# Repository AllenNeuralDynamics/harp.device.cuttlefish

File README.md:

An 8-channel TTL input-or-output device with programmable square wave output

## Features
* 8x TTL input or output, configurable.
* Direct PC control of IO Pins:
  * set pins configured as output to either HIGH (5V) or LOW (0V)
  * read the state of pins configured as inputs as either HIGH (~5V) or LOW (~0V) at TTL logic levels.
* Programmable square wave generation with many configurable settings:
  * PWM Frequency range: from 0.01Hz to 2KHz
  * Duty Cycle
  * Offset
  * number of pulses (or infinite)
* Input Capture. Configure pins as inputs to detect
  * rising edges (up to 500Hz)
  * falling edges (up to 500Hz)
  * both! (up to 500hz)
* Harp-protocol compliant (serial num: 0x057B).
* Bonus: "passthrough buffer mode." External 3.3V and 5V CMOS devices can use this device as an octal buffer with external pins.

> [!NOTE]
> This board produces digital outputs and measures digital inputs only! For producing high fidelity _analog_ outputs, refer to the [harp.device.quac](https://github.com/AllenNeuralDynamics/harp.device.quad-dac) device.

## Extra Features
* 6-24VDC input (2.1 x 5.5mm barrel jack, positive center)
* reverse polarity protection
* soft start
* isolated USB to avoid forming ground loops with the PC.

## PWM Waveform Setup
Each IO pin is capable of producing a PWM output. Here are the settings available:
* _offset_us_: how long (in microseconds) the output should remain LOW before switching the output HIGH in one period.
* _on_duration_us_: how long (in microseconds) the output should remain HIGH in one period.
* _off_duration_us_: how long (in microseconds) the output should remain LOW in one period.
* _cycles_: how many pulses to produce or zero for infinite pulses until disabled.
* _invert_: whether the output should be inverted (on-time refers to the output being LOW instead).

> [!NOTE]
> Although multiple PWM channels can be set to different settings and produce outputs concurrently, all PWM outputs must be started at the same time.

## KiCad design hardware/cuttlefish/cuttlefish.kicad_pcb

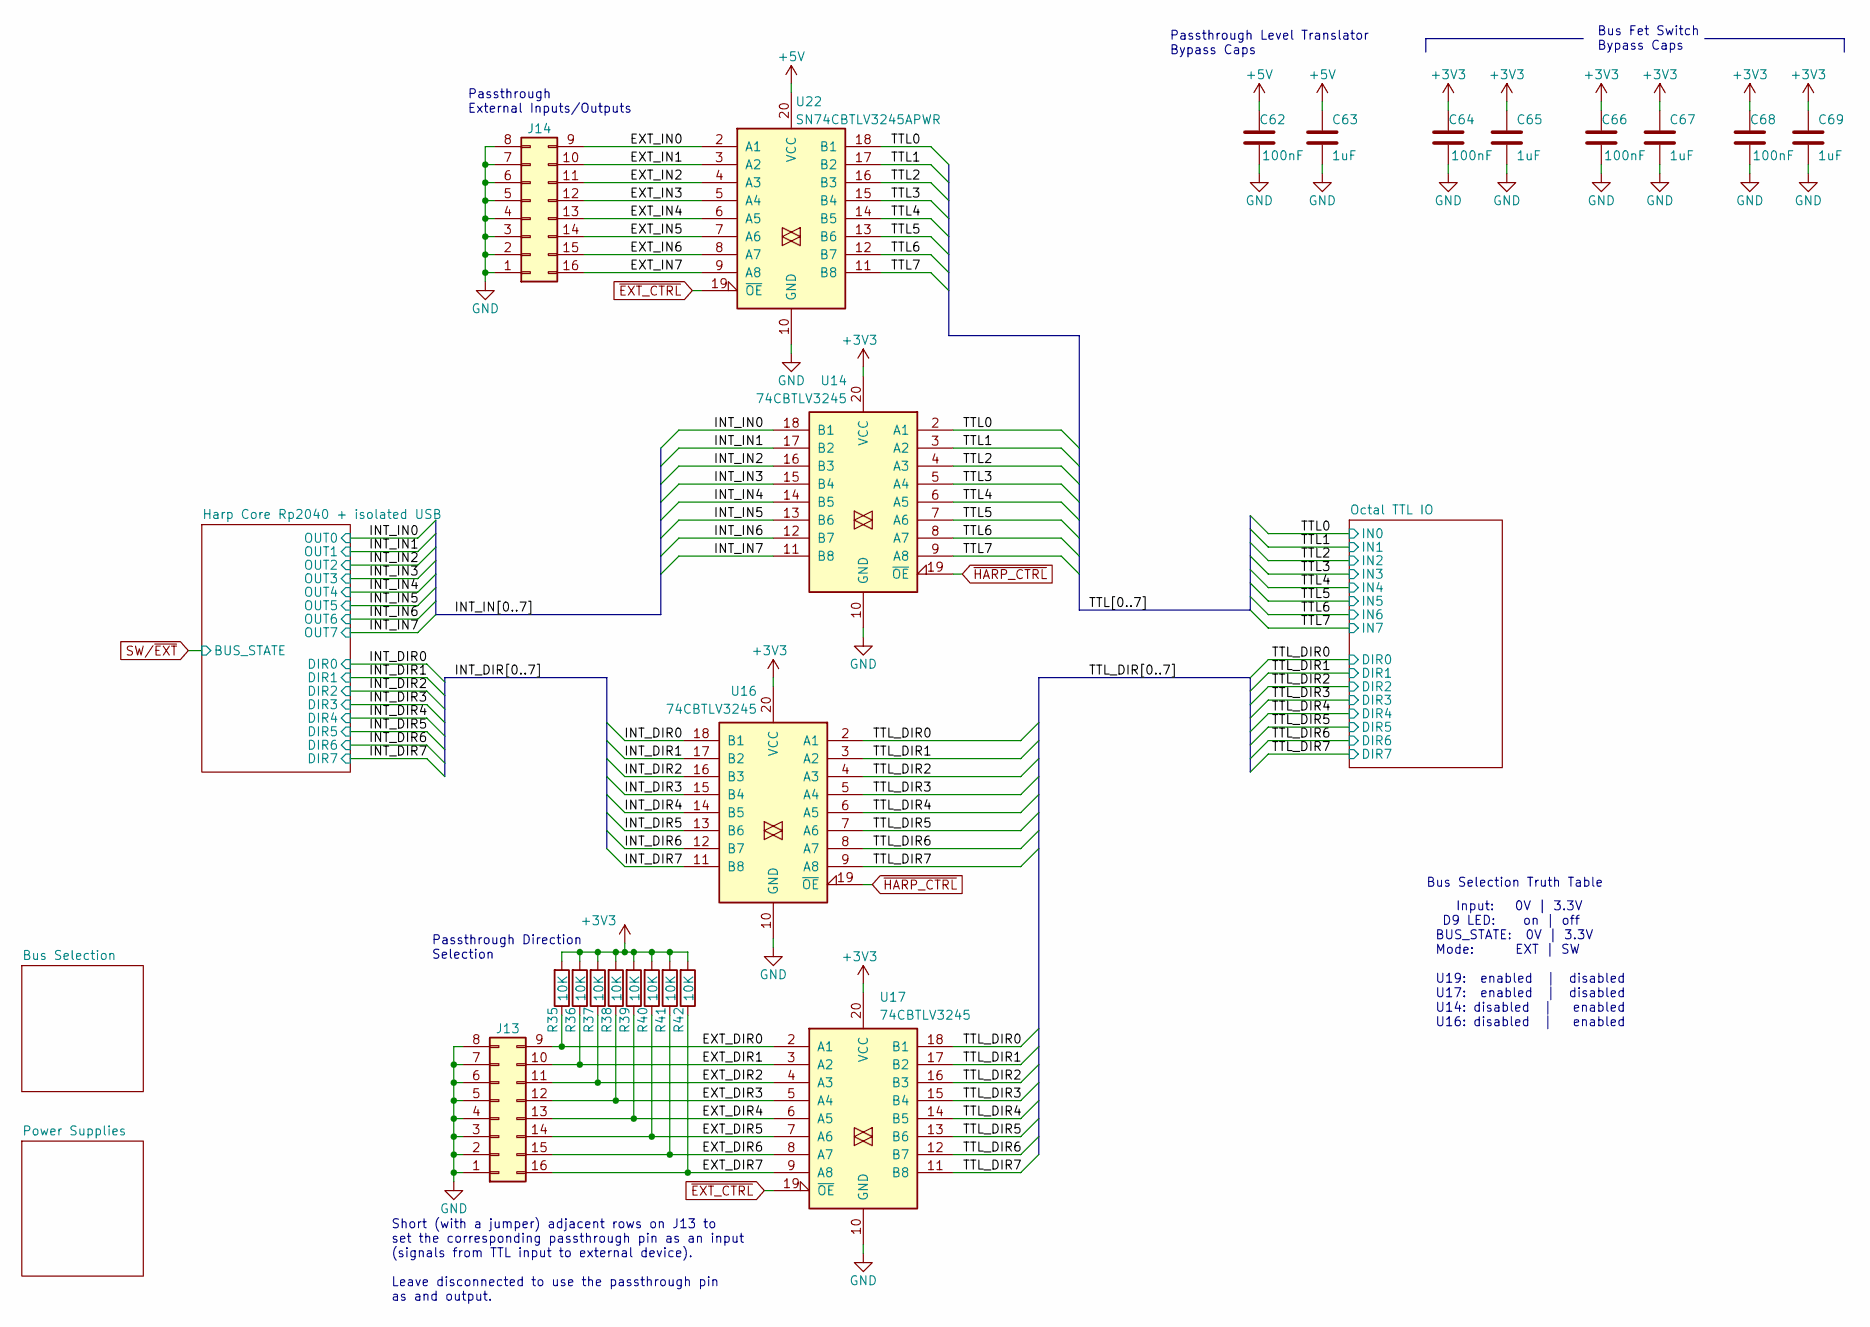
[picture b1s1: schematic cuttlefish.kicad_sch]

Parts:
C62, C64, C66, C68: 100nF; C_0402_1005Metric; Rated Voltage 50V; Tolerance 10%
C63, C65, C67, C69: 1uF; C_0402_1005Metric; Rated Voltage 35V
J13, J14: Conn_02x08_Counter_Clockwise; PinHeader_2x08_P2.54mm_Horizontal_SMD
R35, R36, R37, R38, R39, R40, R41, R42: 10K; R_0402_1005Metric
U14, U16, U17: 74CBTLV3245; TSSOP-20_4.4x6.5mm_P0.65mm
U22: SN74CBTLV3245APWR; TSSOP-20_4.4x6.5mm_P0.65mm

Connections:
+3V3: C64.2, C65.1, C66.2, C67.1, C68.2, C69.1, R35.2, R36.2, R37.2, R38.2, R39.2, R40.2, R41.2, R42.2, U14.20 (VCC), U16.20 (VCC), U17.20 (VCC); also elsewhere on the board
+5V: C62.2, C63.1, U22.20 (VCC); also elsewhere on the board
/EXT_DIR0: J13.9, R35.1, U17.2 (A1)
/EXT_DIR1: J13.10, R36.1, U17.3 (A2)
/EXT_DIR2: J13.11, R37.1, U17.4 (A3)
/EXT_DIR3: J13.12, R38.1, U17.5 (A4)
/EXT_DIR4: J13.13, R39.1, U17.6 (A5)
/EXT_DIR5: J13.14, R40.1, U17.7 (A6)
/EXT_DIR6: J13.15, R41.1, U17.8 (A7)
/EXT_DIR7: J13.16, R42.1, U17.9 (A8)
/EXT_IN0: J14.9, U22.2 (A1)
/EXT_IN1: J14.10, U22.3 (A2)
/EXT_IN2: J14.11, U22.4 (A3)
/EXT_IN3: J14.12, U22.5 (A4)
/EXT_IN4: J14.13, U22.6 (A5)
/EXT_IN5: J14.14, U22.7 (A6)
/EXT_IN6: J14.15, U22.8 (A7)
/EXT_IN7: J14.16, U22.9 (A8)
/INT_DIR0: U16.18 (B1); also elsewhere on the board
/INT_DIR1: U16.17 (B2); also elsewhere on the board
/INT_DIR2: U16.16 (B3); also elsewhere on the board
/INT_DIR3: U16.15 (B4); also elsewhere on the board
/INT_DIR4: U16.14 (B5); also elsewhere on the board
/INT_DIR5: U16.13 (B6); also elsewhere on the board
/INT_DIR6: U16.12 (B7); also elsewhere on the board
/INT_DIR7: U16.11 (B8); also elsewhere on the board
/INT_IN0: U14.18 (B1); also elsewhere on the board
/INT_IN1: U14.17 (B2); also elsewhere on the board
/INT_IN2: U14.16 (B3); also elsewhere on the board
/INT_IN3: U14.15 (B4); also elsewhere on the board
/INT_IN4: U14.14 (B5); also elsewhere on the board
/INT_IN5: U14.13 (B6); also elsewhere on the board
/INT_IN6: U14.12 (B7); also elsewhere on the board
/INT_IN7: U14.11 (B8); also elsewhere on the board
/TTL0: U14.2 (A1), U22.18 (B1); also elsewhere on the board
/TTL1: U14.3 (A2), U22.17 (B2); also elsewhere on the board
/TTL2: U14.4 (A3), U22.16 (B3); also elsewhere on the board
/TTL3: U14.5 (A4), U22.15 (B4); also elsewhere on the board
/TTL4: U14.6 (A5), U22.14 (B5); also elsewhere on the board
/TTL5: U14.7 (A6), U22.13 (B6); also elsewhere on the board
/TTL6: U14.8 (A7), U22.12 (B7); also elsewhere on the board
/TTL7: U14.9 (A8), U22.11 (B8); also elsewhere on the board
/TTL_DIR0: U16.2 (A1), U17.18 (B1); also elsewhere on the board
/TTL_DIR1: U16.3 (A2), U17.17 (B2); also elsewhere on the board
/TTL_DIR2: U16.4 (A3), U17.16 (B3); also elsewhere on the board
/TTL_DIR3: U16.5 (A4), U17.15 (B4); also elsewhere on the board
/TTL_DIR4: U16.6 (A5), U17.14 (B5); also elsewhere on the board
/TTL_DIR5: U16.7 (A6), U17.13 (B6); also elsewhere on the board
/TTL_DIR6: U16.8 (A7), U17.12 (B7); also elsewhere on the board
/TTL_DIR7: U16.9 (A8), U17.11 (B8); also elsewhere on the board
GND: C62.1, C63.2, C64.1, C65.2, C66.1, C67.2, C68.1, C69.2, J13.1, J13.2, J13.3, J13.4, J13.5, J13.6, J13.7, J13.8, J14.1, J14.2, J14.3, J14.4, J14.5, J14.6, J14.7, J14.8, U14.10 (GND), U16.10 (GND), U17.10 (GND), U22.10 (GND); also elsewhere on the board
~EXT_CTRL: U17.19 (~OE), U22.19 (~OE); also elsewhere on the board
~HARP_CTRL: U14.19 (~OE), U16.19 (~OE); also elsewhere on the board

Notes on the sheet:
Passthrough External Inputs/Outputs
Input: 0V | 3.3V D9 LED: on | off BUS_STATE: 0V | 3.3V Mode: EXT | SW U19: enabled | disabled U17: enabled | disabled U14: disabled | enabled U16: disabled | enabled
Passthrough Direction Selection
Bus Fet Switch Bypass Caps
Short (with a jumper) adjacent rows on J13 to set the corresponding passthrough pin as an input (signals from TTL input to external device). Leave disconnected to use the passthrough pin as and output.
Passthrough Level Translator Bypass Caps
Bus Selection Truth Table

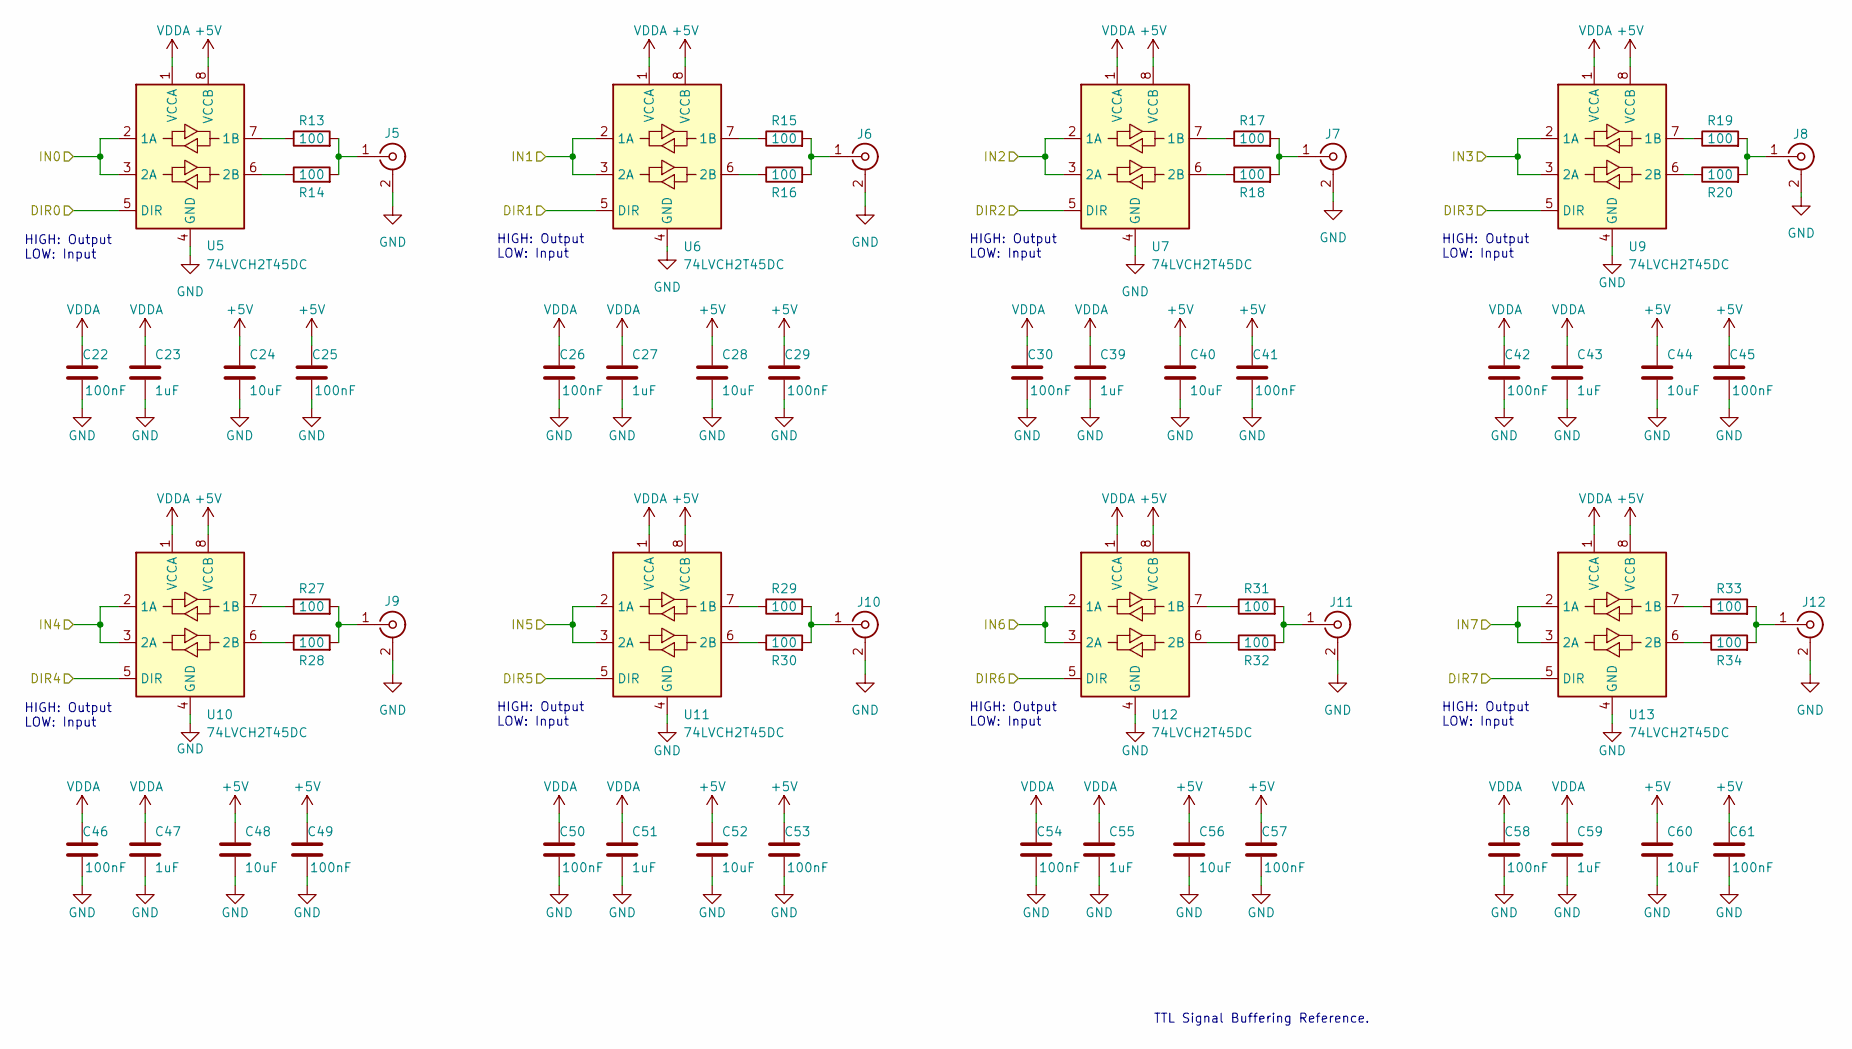
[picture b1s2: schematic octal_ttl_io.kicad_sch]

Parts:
C22, C25, C26, C29, C30, C41, C42, C45, C46, C49, C50, C53, C54, C57, C58, C61: 100nF; C_0402_1005Metric; Rated Voltage 50V; Tolerance 10%
C23, C27, C39, C43, C47, C51, C55, C59: 1uF; C_0402_1005Metric; Rated Voltage 35V
C24, C28, C40, C44, C48, C52, C56, C60: 10uF; C_0805_2012Metric; Rated Voltage 25V
J5, J6, J7, J8, J9, J10, J11, J12: Conn_Coaxial; BNC_AmphenolRF_031-5329-52RFX_Vertical
R13, R14, R15, R16, R17, R18, R19, R20, R27, R28, R29, R30, R31, R32, R33, R34: 100; R_0402_1005Metric; Tolerance 1%
U5, U6, U7, U9, U10, U11, U12, U13: 74LVCH2T45DC; VSSOP-8_2.3x2mm_P0.5mm_TexasInstruments

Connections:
+5V: C24.1, C25.2, C28.1, C29.2, C40.1, C41.2, C44.1, C45.2, C48.1, C49.2, C52.1, C53.2, C56.1, C57.2, C60.1, C61.2, U5.8 (VCCB), U6.8 (VCCB), U7.8 (VCCB), U9.8 (VCCB), U10.8 (VCCB), U11.8 (VCCB), U12.8 (VCCB), U13.8 (VCCB); also elsewhere on the board
/TTL0: U5.2 (1A), U5.3 (2A); also elsewhere on the board
/TTL1: U6.2 (1A), U6.3 (2A); also elsewhere on the board
/TTL2: U7.2 (1A), U7.3 (2A); also elsewhere on the board
/TTL3: U9.2 (1A), U9.3 (2A); also elsewhere on the board
/TTL4: U10.2 (1A), U10.3 (2A); also elsewhere on the board
/TTL5: U11.2 (1A), U11.3 (2A); also elsewhere on the board
/TTL6: U12.2 (1A), U12.3 (2A); also elsewhere on the board
/TTL7: U13.2 (1A), U13.3 (2A); also elsewhere on the board
/TTL_DIR0: U5.5 (DIR); also elsewhere on the board
/TTL_DIR1: U6.5 (DIR); also elsewhere on the board
/TTL_DIR2: U7.5 (DIR); also elsewhere on the board
/TTL_DIR3: U9.5 (DIR); also elsewhere on the board
/TTL_DIR4: U10.5 (DIR); also elsewhere on the board
/TTL_DIR5: U11.5 (DIR); also elsewhere on the board
/TTL_DIR6: U12.5 (DIR); also elsewhere on the board
/TTL_DIR7: U13.5 (DIR); also elsewhere on the board
GND: C22.1, C23.2, C24.2, C25.1, C26.1, C27.2, C28.2, C29.1, C30.1, C39.2, C40.2, C41.1, C42.1, C43.2, C44.2, C45.1, C46.1, C47.2, C48.2, C49.1, C50.1, C51.2, C52.2, C53.1, C54.1, C55.2, C56.2, C57.1, C58.1, C59.2, C60.2, C61.1, J5.2 (Ext), J6.2 (Ext), J7.2 (Ext), J8.2 (Ext), J9.2 (Ext), J10.2 (Ext), J11.2 (Ext), J12.2 (Ext), U5.4 (GND), U6.4 (GND), U7.4 (GND), U9.4 (GND), U10.4 (GND), U11.4 (GND), U12.4 (GND), U13.4 (GND); also elsewhere on the board
unnamed: J5.1 (In), R13.2, R14.2
unnamed: J6.1 (In), R15.2, R16.2
unnamed: J7.1 (In), R17.2, R18.2
unnamed: J8.1 (In), R19.2, R20.2
unnamed: J9.1 (In), R27.2, R28.2
unnamed: J10.1 (In), R29.2, R30.2
unnamed: J11.1 (In), R31.2, R32.2
unnamed: J12.1 (In), R33.2, R34.2
unnamed: R13.1, U5.7 (1B)
unnamed: R14.1, U5.6 (2B)
unnamed: R15.1, U6.7 (1B)
unnamed: R16.1, U6.6 (2B)
unnamed: R17.1, U7.7 (1B)
unnamed: R18.1, U7.6 (2B)
unnamed: R19.1, U9.7 (1B)
unnamed: R20.1, U9.6 (2B)
unnamed: R27.1, U10.7 (1B)
unnamed: R28.1, U10.6 (2B)
unnamed: R29.1, U11.7 (1B)
unnamed: R30.1, U11.6 (2B)
unnamed: R31.1, U12.7 (1B)
unnamed: R32.1, U12.6 (2B)
unnamed: R33.1, U13.7 (1B)
unnamed: R34.1, U13.6 (2B)
VDDA: C22.2, C23.1, C26.2, C27.1, C30.2, C39.1, C42.2, C43.1, C46.2, C47.1, C50.2, C51.1, C54.2, C55.1, C58.2, C59.1, U5.1 (VCCA), U6.1 (VCCA), U7.1 (VCCA), U9.1 (VCCA), U10.1 (VCCA), U11.1 (VCCA), U12.1 (VCCA), U13.1 (VCCA); also elsewhere on the board

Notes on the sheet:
HIGH: Output LOW: Input
TTL Signal Buffering Reference.

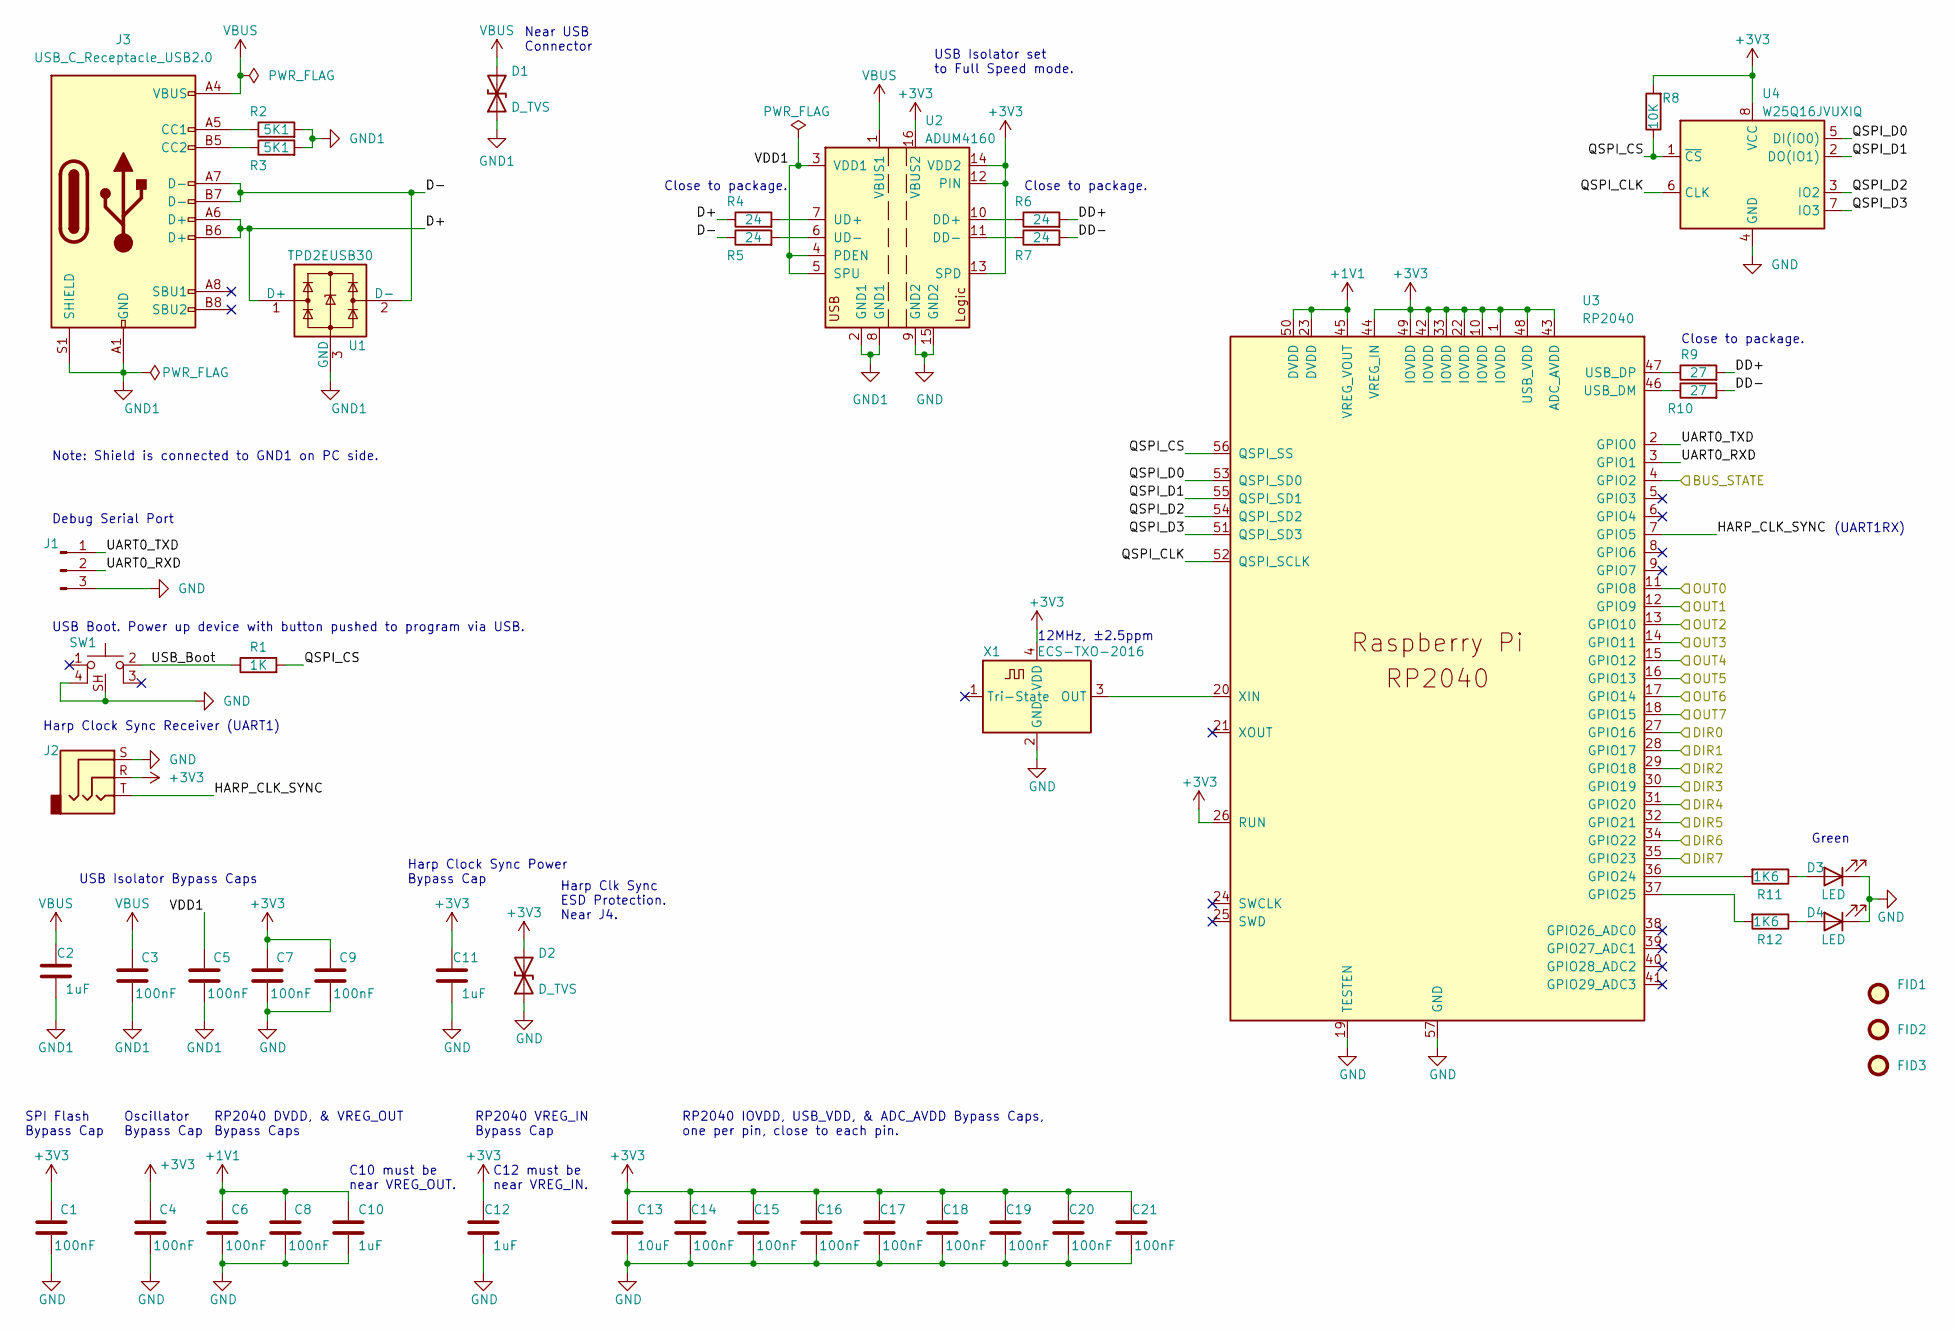
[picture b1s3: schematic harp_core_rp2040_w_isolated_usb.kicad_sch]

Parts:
C1, C3, C4, C5, C6, C7, C8, C9, C14, C15, C16, C17, C18, C19, C20, C21: 100nF; C_0402_1005Metric; Rated Voltage 50V; Tolerance 10%
C2, C10, C11, C12: 1uF; C_0402_1005Metric; Rated Voltage 35V
C13: 10uF; C_0805_2012Metric; Rated Voltage 25V
D1, D2: D_TVS; D_0402_1005Metric
D3, D4: LED; LED_0603_1608Metric
FID1, FID2, FID3: Fiducial; Fiducial_0.5mm_Mask1mm
J1: Conn_01x03_Male; PinHeader_1x03_P2.54mm_Vertical
J2: AudioJack3; Jack_3.5mm_CUI_SJ-3523-SMT_Horizontal
J3: USB_C_Receptacle_USB2.0; USB_C_Receptacle_JAE_DX07S016JA1R1500
R1: 1K; R_0402_1005Metric; Tolerance 1%
R2, R3: 5K1; R_0402_1005Metric; Tolerance 1%
R4, R5, R6, R7: 24; R_0402_1005Metric; Tolerance 1%
R8: 10K; R_0402_1005Metric
R9, R10: 27; R_0402_1005Metric; Tolerance 1%
R11, R12: 1K6; R_0402_1005Metric
SW1: SW_Push_1P1T-SH_NO_Vertical_Wuerth_WS-TASV
U1: TPD2EUSB30; Texas_DRT-3
U2: ADUM4160; SOIC-16W_7.5x10.3mm_P1.27mm
U3: RP2040; RP2040-QFN-56
U4: W25Q16JVUXIQ; Winbond-8USON-2x3mm
X1: ECS-TXO-2016; Crystal_SMD_2016-4Pin_2.0x1.6mm; Tolerance ±2.5ppm

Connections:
+1V1: C6.2, C8.2, C10.1, U3.23 (DVDD), U3.45 (VREG_VOUT), U3.50 (DVDD)
+3V3: C1.2, C4.2, C7.2, C9.2, C11.1, C12.1, C13.1, C14.2, C15.2, C16.2, C17.2, C18.2, C19.2, C20.2, C21.2, D2.2 (A2), J2.R, R8.2, U2.12 (PIN), U2.13 (SPD), U2.14 (VDD2), U2.16 (VBUS2), U3.1 (IOVDD), U3.10 (IOVDD), U3.22 (IOVDD), U3.26 (RUN), U3.33 (IOVDD), U3.42 (IOVDD), U3.43 (ADC_AVDD), U3.44 (VREG_IN), U3.48 (USB_VDD), U3.49 (IOVDD), U4.8 (VCC), X1.4 (VDD); also elsewhere on the board
/Harp Core Rp2040 + isolated USB/D+: J3.A6 (D+), J3.B6 (D+), R4.1, U1.1 (D+)
/Harp Core Rp2040 + isolated USB/D-: J3.A7 (D-), J3.B7 (D-), R5.1, U1.2 (D-)
/Harp Core Rp2040 + isolated USB/DD+: R6.2, R9.2
/Harp Core Rp2040 + isolated USB/DD-: R7.2, R10.2
/Harp Core Rp2040 + isolated USB/HARP_CLK_SYNC: J2.T, U3.7 (GPIO5)
/Harp Core Rp2040 + isolated USB/QSPI_CLK: U3.52 (QSPI_SCLK), U4.6 (CLK)
/Harp Core Rp2040 + isolated USB/QSPI_CS: R1.2, R8.1, U3.56 (QSPI_SS), U4.1 (~CS)
/Harp Core Rp2040 + isolated USB/QSPI_D0: U3.53 (QSPI_SD0), U4.5 (DI(IO0))
/Harp Core Rp2040 + isolated USB/QSPI_D1: U3.55 (QSPI_SD1), U4.2 (DO(IO1))
/Harp Core Rp2040 + isolated USB/QSPI_D2: U3.54 (QSPI_SD2), U4.3 (IO2)
/Harp Core Rp2040 + isolated USB/QSPI_D3: U3.51 (QSPI_SD3), U4.7 (IO3)
/Harp Core Rp2040 + isolated USB/UART0_RXD: J1.2, U3.3 (GPIO1)
/Harp Core Rp2040 + isolated USB/UART0_TXD: J1.1, U3.2 (GPIO0)
/Harp Core Rp2040 + isolated USB/USB_Boot: R1.1, SW1.2
/Harp Core Rp2040 + isolated USB/VDD1: C5.2, U2.3 (VDD1), U2.4 (PDEN), U2.5 (SPU)
/INT_DIR0: U3.27 (GPIO16); also elsewhere on the board
/INT_DIR1: U3.28 (GPIO17); also elsewhere on the board
/INT_DIR2: U3.29 (GPIO18); also elsewhere on the board
/INT_DIR3: U3.30 (GPIO19); also elsewhere on the board
/INT_DIR4: U3.31 (GPIO20); also elsewhere on the board
/INT_DIR5: U3.32 (GPIO21); also elsewhere on the board
/INT_DIR6: U3.34 (GPIO22); also elsewhere on the board
/INT_DIR7: U3.35 (GPIO23); also elsewhere on the board
/INT_IN0: U3.11 (GPIO8); also elsewhere on the board
/INT_IN1: U3.12 (GPIO9); also elsewhere on the board
/INT_IN2: U3.13 (GPIO10); also elsewhere on the board
/INT_IN3: U3.14 (GPIO11); also elsewhere on the board
/INT_IN4: U3.15 (GPIO12); also elsewhere on the board
/INT_IN5: U3.16 (GPIO13); also elsewhere on the board
/INT_IN6: U3.17 (GPIO14); also elsewhere on the board
/INT_IN7: U3.18 (GPIO15); also elsewhere on the board
GND: C1.1, C4.1, C6.1, C7.1, C8.1, C9.1, C10.2, C11.2, C12.2, C13.2, C14.1, C15.1, C16.1, C17.1, C18.1, C19.1, C20.1, C21.1, D2.1 (A1), D3.1 (K), D4.1 (K), J1.3, J2.S, SW1.4, SW1.SH, U2.9 (GND2), U2.15 (GND2), U3.19 (TESTEN), U3.57 (GND), U4.4 (GND), X1.2 (GND); also elsewhere on the board
GND1: C2.2, C3.1, C5.1, D1.1 (A1), J3.A1 (GND), J3.A12 (GND), J3.B1 (GND), J3.B12 (GND), J3.S1 (SHIELD), R2.2, R3.2, U1.3 (GND), U2.2 (GND1), U2.8 (GND1)
unnamed: D3.2 (A), R11.1
unnamed: D4.2 (A), R12.1
unnamed: J3.A5 (CC1), R2.1
unnamed: J3.B5 (CC2), R3.1
unnamed: R6.1, U2.10 (DD+)
unnamed: R7.1, U2.11 (DD-)
unnamed: R4.2, U2.7 (UD+)
unnamed: R5.2, U2.6 (UD-)
unnamed: R11.2, U3.36 (GPIO24)
unnamed: R12.2, U3.37 (GPIO25)
unnamed: R10.1, U3.46 (USB_DM)
unnamed: R9.1, U3.47 (USB_DP)
unnamed: U3.20 (XIN), X1.3 (OUT)
SW/~EXT: U3.4 (GPIO2); also elsewhere on the board
VBUS: C2.1, C3.2, D1.2 (A2), J3.A4 (VBUS), J3.A9 (VBUS), J3.B4 (VBUS), J3.B9 (VBUS), U2.1 (VBUS1)

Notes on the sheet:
USB Isolator Bypass Caps
Near USB Connector
Close to package.
Harp Clock Sync Power Bypass Cap
USB Isolator set to Full Speed mode.
12MHz, ±2.5ppm
Debug Serial Port
USB Boot. Power up device with button pushed to program via USB.
(UART1RX)
Harp Clock Sync Receiver (UART1)
Note: Shield is connected to GND1 on PC side.
RP2040 DVDD, & VREG_OUT Bypass Caps
RP2040 IOVDD, USB_VDD, & ADC_AVDD Bypass Caps, one per pin, close to each pin.
C10 must be near VREG_OUT.
RP2040 VREG_IN Bypass Cap
SPI Flash Bypass Cap
Harp Clk Sync ESD Protection. Near J4.
Oscillator Bypass Cap
C12 must be near VREG_IN.
Green

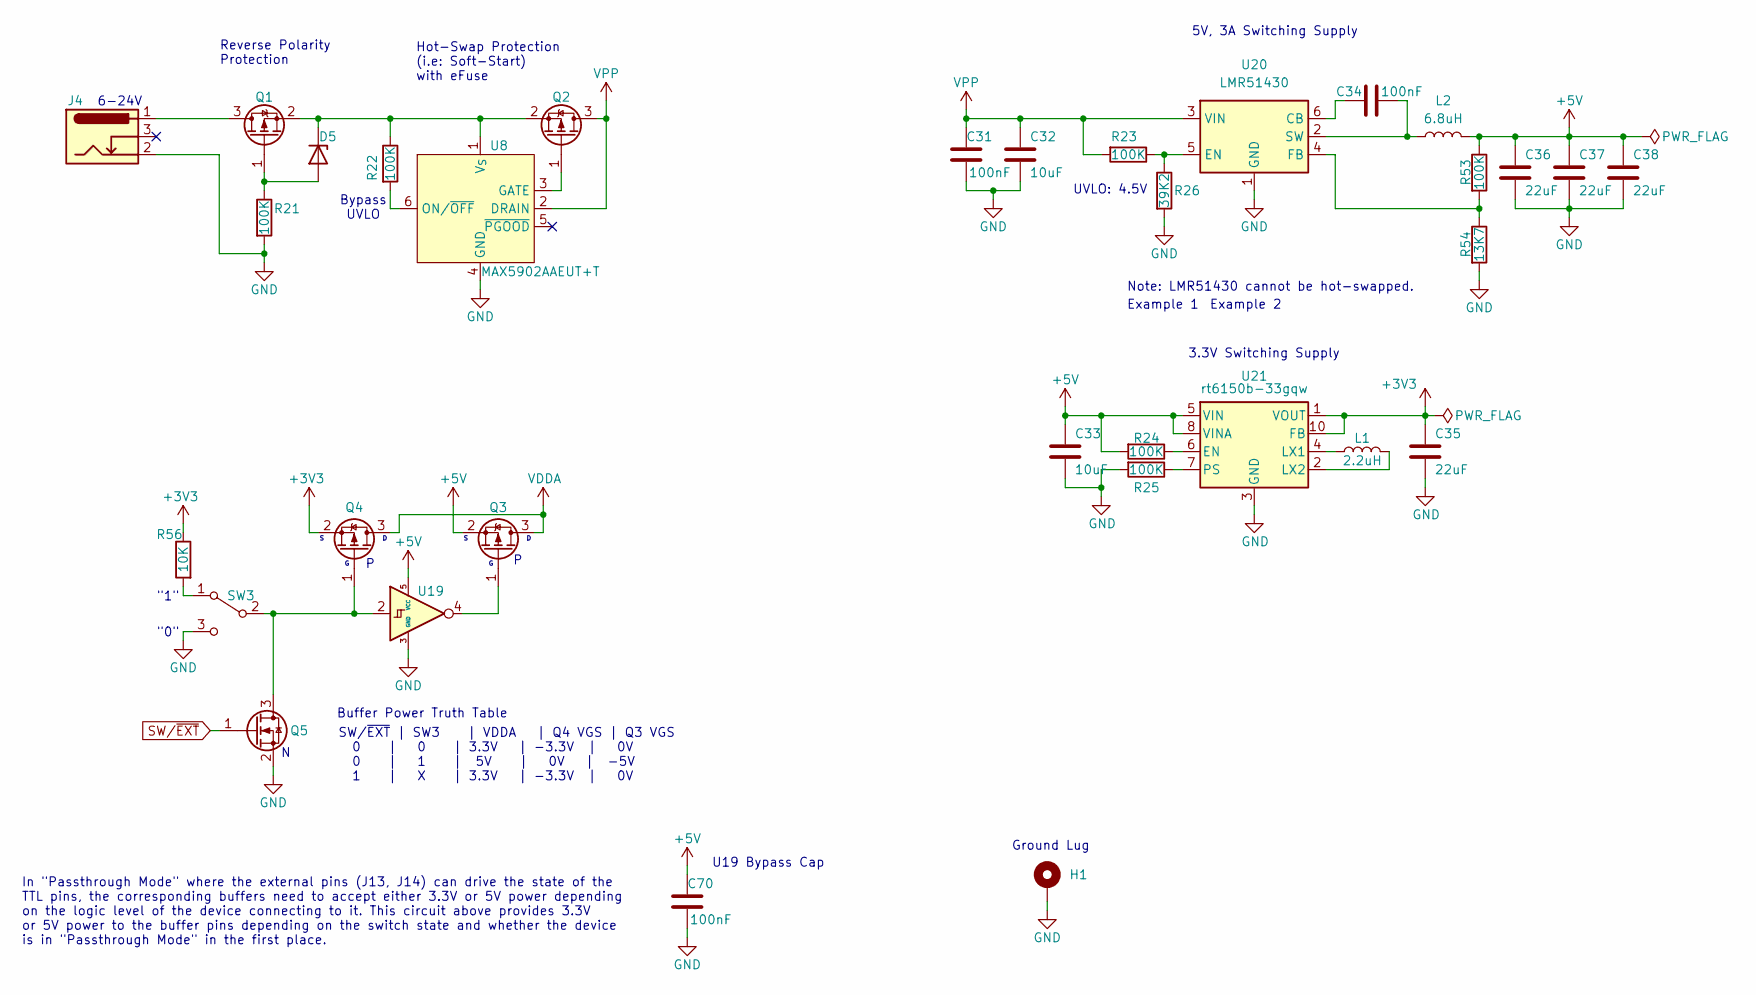
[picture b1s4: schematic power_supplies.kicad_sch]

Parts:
C31, C34, C70: 100nF; C_0402_1005Metric; Rated Voltage 50V; Tolerance 10%
C32, C33: 10uF; C_0805_2012Metric; Rated Voltage 25V
C35, C36, C37, C38: 22uF; C_0805_2012Metric; Rated Voltage 25V
D5: BZV55B15; D_MiniMELF
H1: MountingHole_Pad; Terminal_Keystone_779x_EdgeMount_Horizontal
J4: Barrel_Jack_Switch; BarrelJack_Same_Sky_PJ-102AH_Horizontal
L1: 2.2uH; L_0603_1608Metric
L2: 6.8uH; L_Bourns-SRP4030FA
Q1, Q2, Q3, Q4: Si2369DS; SOT-23
Q5: DMN2040U; SOT-23
R21, R22, R23, R24, R25, R53: 100K; R_0402_1005Metric; Tolerance 1%
R26: 39K2; R_0402_1005Metric; Tolerance 1%
R54: 13K7; R_0402_1005Metric; Tolerance 1%
R56: 10K; R_0402_1005Metric
SW3: SW_SPDT; SW_SPDT_CK-JS102011SAQN
U8: MAX5902AAEUT+T; SOT-23-6
U19: SN74LVC1G14DRL; SOT-553
U20: LMR51430; SOT-23-6
U21: rt6150b-33gqw; WDFN-10-1EP_2.5x2.5mm_P0.5_EP1.25x2.1mm

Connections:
+3V3: C35.1, Q4.2 (S), R56.1, U21.1 (VOUT), U21.10 (FB); also elsewhere on the board
+5V: C33.1, C36.1, C37.1, C38.1, C70.2, L2.2, Q3.2 (S), R24.2, R53.1, U19.5 (VCC), U21.5 (VIN), U21.8 (VINA); also elsewhere on the board
GND: C31.1, C32.2, C33.2, C35.2, C36.2, C37.2, C38.2, C70.1, H1.1, J4.2, Q5.2 (S), R21.2, R25.2, R26.2, R54.2, SW3.3 (C), U8.4 (GND), U19.3 (GND), U20.1 (GND), U21.3 (GND), U21.9 (GND), U21.11 (GND); also elsewhere on the board
unnamed: D5.2 (A), Q1.1 (G), R21.1
unnamed: D5.1 (K), Q1.2 (S), Q2.2 (S), R22.1, U8.1 (V_{S})
unnamed: J4.1, Q1.3 (D)
unnamed: Q2.1 (G), U8.3 (GATE)
unnamed: Q3.1 (G), U19.4
unnamed: Q4.1 (G), Q5.3 (D), SW3.2 (B), U19.2
unnamed: R56.2, SW3.1 (A)
unnamed: R22.2, U8.6 (ON/~OFF)
unnamed: C34.2, U20.6 (CB)
unnamed: R23.1, R26.1, U20.5 (EN)
unnamed: R53.2, R54.1, U20.4 (FB)
unnamed: C34.1, L2.1, U20.2 (SW)
unnamed: R24.1, U21.6 (EN)
unnamed: L1.1, U21.4 (LX1)
unnamed: L1.2, U21.2 (LX2)
unnamed: R25.1, U21.7 (PS)
SW/~EXT: Q5.1 (G); also elsewhere on the board
VDDA: Q3.3 (D), Q4.3 (D); also elsewhere on the board
VPP: C31.2, C32.1, Q2.3 (D), R23.2, U8.2 (DRAIN), U20.3 (VIN)

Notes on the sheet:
U19 Bypass Cap
Example 2
5V, 3A Switching Supply
"1"
"0"
Example 1
Bypass UVLO
Note: LMR51430 cannot be hot-swapped.
Buffer Power Truth Table
UVLO: 4.5V
Hot-Swap Protection (i.e: Soft-Start) with eFuse
6-24V
In "Passthrough Mode" where the external pins (J13, J14) can drive the state of the TTL pins, the corresponding buffers need to accept either 3.3V or 5V power depending on the logic level of the device connecting to it. This circuit above provides 3.3V or 5V power to the buffer pins depending on th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
SW/~{EXT} | SW3 | VDDA | Q4 VGS | Q3 VGS 0 | 0 | 3.3V | -3.3V | 0V 0 | 1 | 5V | 0V | -5V 1 | X | 3.3V | -3.3V | 0V
Ground Lug
3.3V Switching Supply
Reverse Polarity Protection

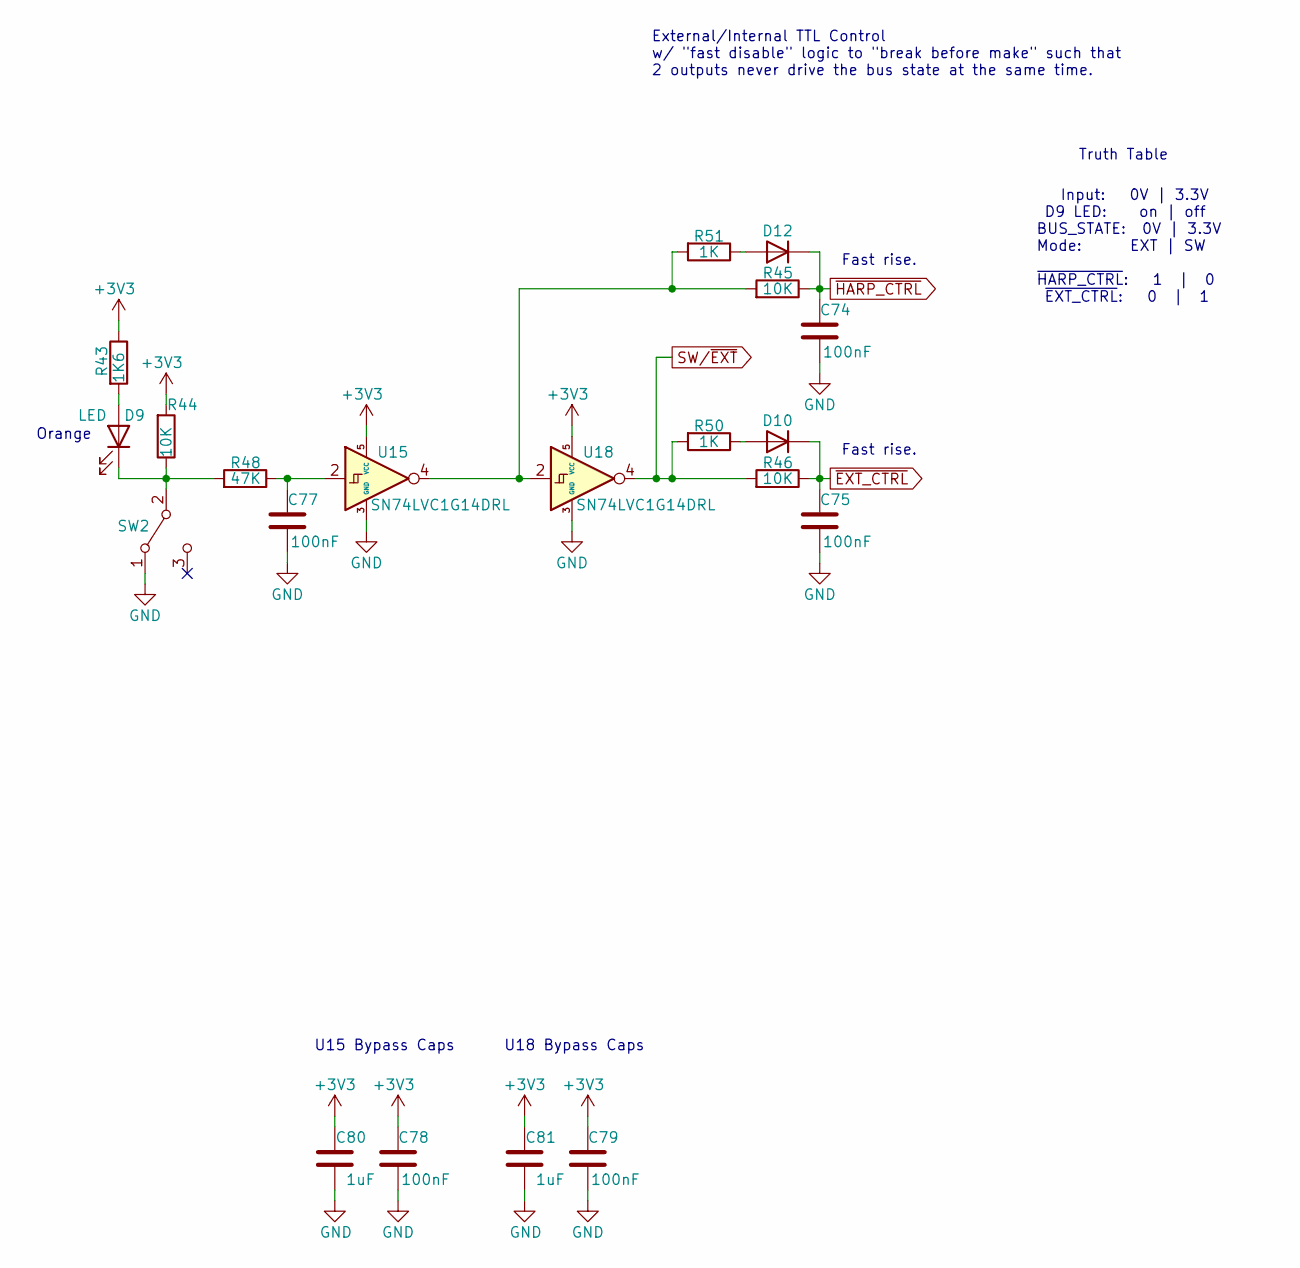
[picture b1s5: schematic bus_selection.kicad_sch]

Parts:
C74, C75, C77, C78, C79: 100nF; C_0402_1005Metric; Rated Voltage 50V; Tolerance 10%
C80, C81: 1uF; C_0402_1005Metric; Rated Voltage 35V
D9: LED; LED_0603_1608Metric
D10, D12: NSR05F40NXT5G; D_0402_1005Metric
R43: 1K6; R_0402_1005Metric
R44, R45, R46: 10K; R_0402_1005Metric
R48: 47K; R_0402_1005Metric; Tolerance 1%
R50, R51: 1K; R_0402_1005Metric; Tolerance 1%
SW2: SW_SPDT; SW_SPDT_CK-JS102011SAQN
U15, U18: SN74LVC1G14DRL; SOT-553

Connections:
+3V3: C78.2, C79.2, C80.1, C81.1, R43.1, R44.2, U15.5 (VCC), U18.5 (VCC); also elsewhere on the board
GND: C74.1, C75.1, C77.1, C78.1, C79.1, C80.2, C81.2, SW2.1 (A), U15.3 (GND), U18.3 (GND); also elsewhere on the board
unnamed: C77.2, R48.1, U15.2
unnamed: D9.2 (A), R43.2
unnamed: D9.1 (K), R44.1, R48.2, SW2.2 (B)
unnamed: D10.2 (A), R50.1
unnamed: D12.2 (A), R51.1
unnamed: R45.2, R51.2, U15.4, U18.2
SW/~EXT: R46.2, R50.2, U18.4; also elsewhere on the board
~EXT_CTRL: C75.2, D10.1 (K), R46.1; also elsewhere on the board
~HARP_CTRL: C74.2, D12.1 (K), R45.1; also elsewhere on the board

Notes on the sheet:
Truth Table
External/Internal TTL Control w/ "fast disable" logic to "break before make" such that 2 outputs never drive the bus state at the same time.
U18 Bypass Caps
Input: 0V | 3.3V D9 LED: on | off BUS_STATE: 0V | 3.3V Mode: EXT | SW ~{HARP_CTRL}: 1 | 0 ~{EXT_CTRL}: 0 | 1
U15 Bypass Caps
Fast rise.
Orange

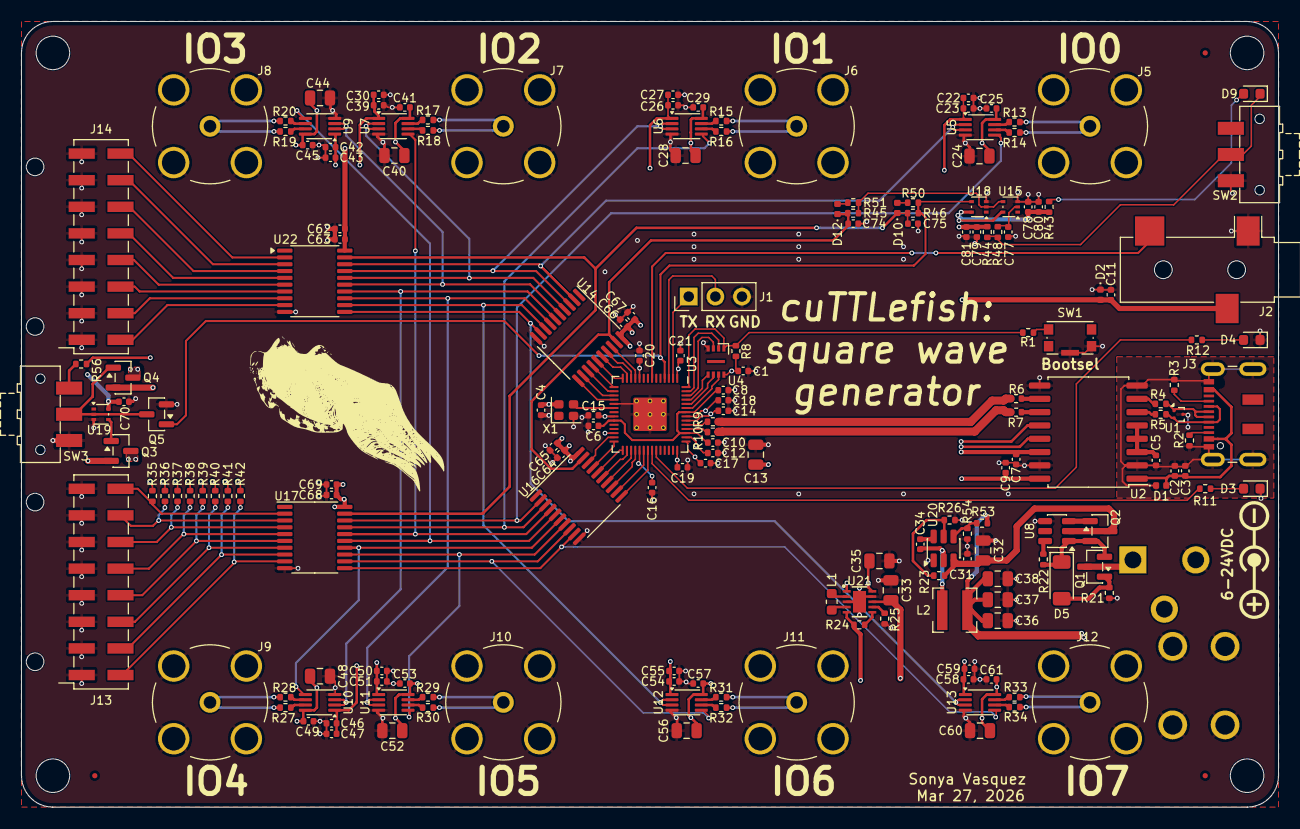
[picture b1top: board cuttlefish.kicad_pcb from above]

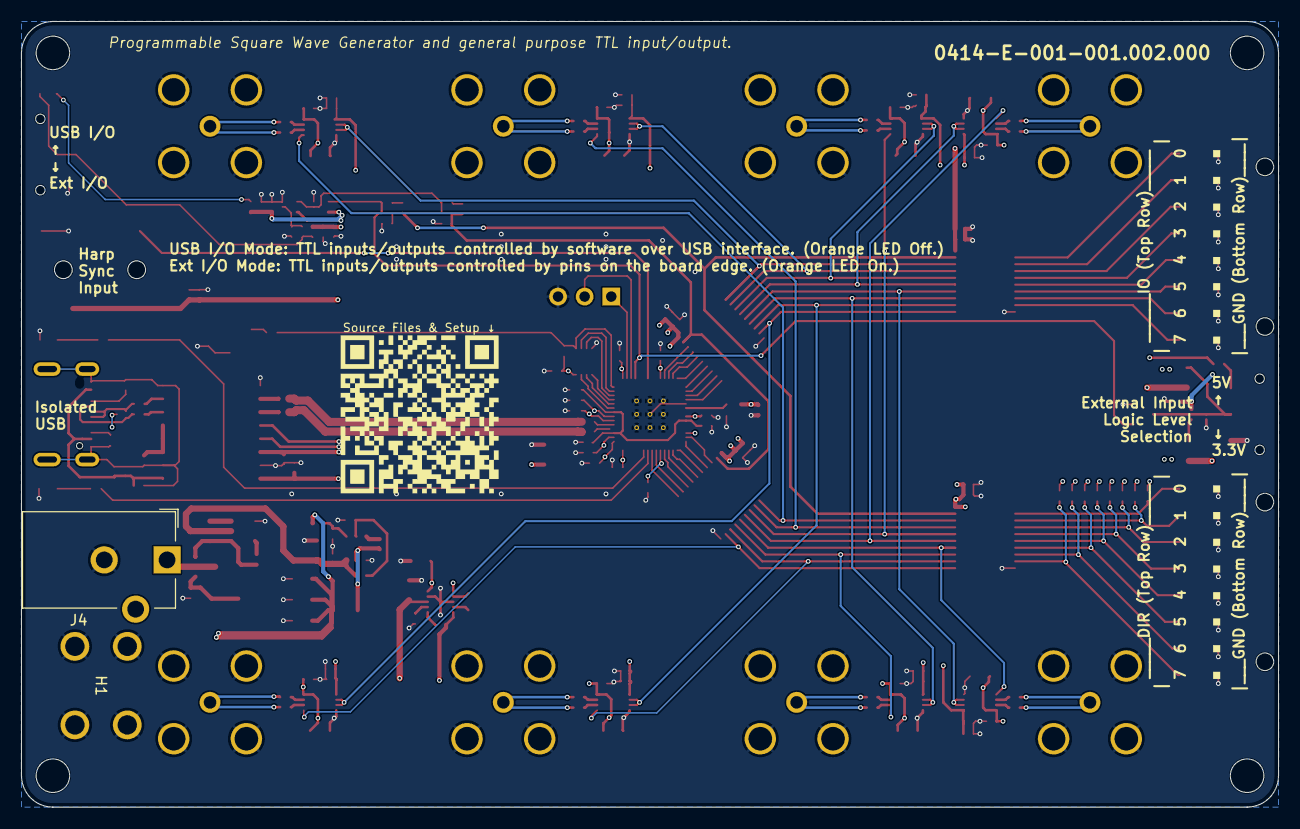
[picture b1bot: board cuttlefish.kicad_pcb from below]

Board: 4 copper layers, 120.0 x 75.0 mm, 189 parts (2 on the bottom side), 133 nets.

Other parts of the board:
G3: LOGO
